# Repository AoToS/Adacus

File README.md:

# Mixed signal PCB with op-amps, filters, ADC/DAC interfaces. ADACUS

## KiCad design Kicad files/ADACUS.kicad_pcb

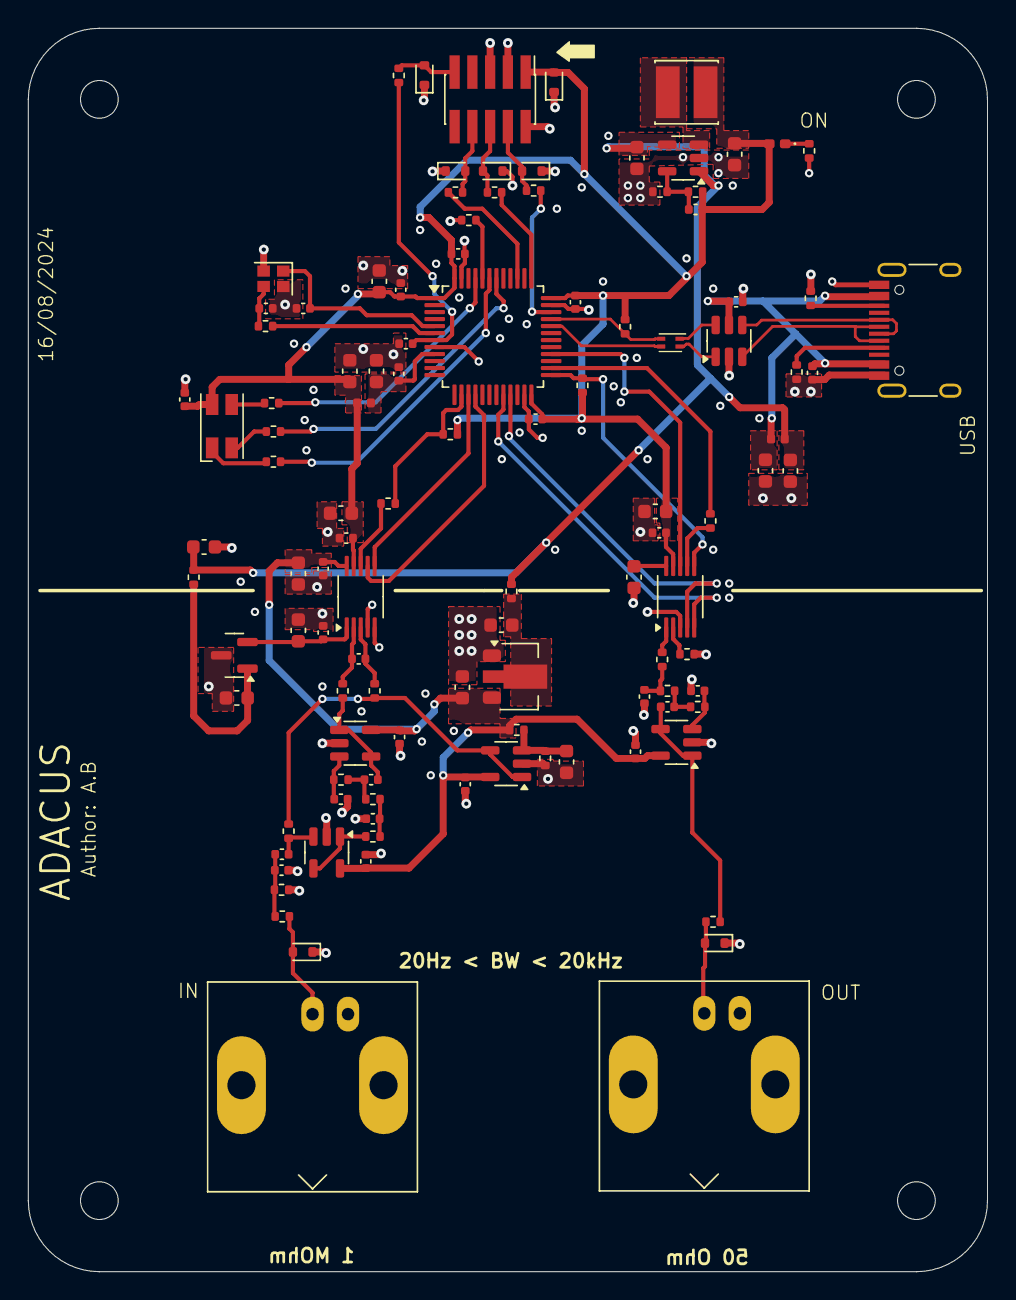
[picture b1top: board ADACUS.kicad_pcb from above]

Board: 4 copper layers, 68.6 x 88.9 mm, 115 parts (0 on the bottom side), 68 nets.

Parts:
C100, C101, C206, C207, C402: 1u; C_0603_1608Metric
C102, C103, C104, C105, C107: 22u; C_0603_1608Metric
C106: DNP; C_0402_1005Metric
C108, C201, C202, C203, C204, C210, C211, C212, C213, C303, C305, C306, C309, C310, C314, C401, C406: 100n; C_0402_1005Metric
C200, C300, C301, C302, C304, C307, C400: 10u; C_0603_1608Metric
C205: 10n; C_0402_1005Metric
C208, C209: 10p; C_0402_1005Metric
C308, C311, C312, C315, C403, C404: 150p; C_0402_1005Metric
C313, C405: 1n; C_0402_1005Metric
D100: LED; D_0402_1005Metric_Pad0.77x0.64mm_HandSolder
D200: ASMB-MTB0-0A3A2; LED_RGB_Wuerth-PLCC4_3.2x2.8mm_150141M173100
D201, D202, D203, D204, D205, D300, D400: PESD3V3L1UB,115; D_SOD-523
FL200: CMF3216F-900-2P-T; L_CommonModeChoke_Coilcraft_0603USB
H100, H101, H102, H103: MountingHole; MountingHole_2.7mm
J200: USB_C_Receptacle_USB2.0_14P; USB_C_Receptacle_HRO_TYPE-C-31-M-12
J201: PinHeader_2x05_P1.27mm_Vertical_SMD
J300, J400: BNC_Amphenol_B6252HB-NPP3G-50_Horizontal
L100, L200: 10n; L_0402_1005Metric
L101: 68u; L_Cenker_CKCS4020
R100: 10R; R_0402_1005Metric
R101: 100k; R_0402_1005Metric
R102: 22k; R_0402_1005Metric
R103, R104, R105: 1K; R_0402_1005Metric
R200, R202, R203: 10K; R_0402_1005Metric
R201, R301, R400: 0R; R_0402_1005Metric
R204: 1k5; R_0402_1005Metric
R205, R206, R207, R208, R300: 49R9; R_0402_1005Metric
R209, R210, R211, R302, R308, R309: 1k; R_0402_1005Metric
R212, R213: 5k1; R_0402_1005Metric
R303, R304: 2M2; R_0402_1005Metric
R305, R306, R307, R402, R403, R404, R405: 6k8; R_0402_1005Metric
R401: 10k; R_0402_1005Metric
U100: HT7533-1; SOT-89-3
U101: TLV62569DBV; SOT-23-5
U102: MCP6001-E/OT; SOT-23-5
U200: STM32F103CBT6; LQFP-48_7x7mm_P0.5mm
U201: USBLC6-2SC6; SOT-23-6
U300, U400: VSSOP-10_3x3mm_P0.5mm
U301: REF3033; SOT-23
U302, U303, U401: MCP6001UT-E/OT; SOT-23-5
Y200: 16MHz; Crystal_SMD_2016-4Pin_2.0x1.6mm

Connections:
+3.3VA: C103.1, C108.2, C304.1, C305.1, C310.2, C314.2, C406.2, R104.1, U100.3 (VOUT), U102.5 (V+), U300.10 (VA), U302.5 (V+), U303.5 (V+), U401.5 (V+)
+3V3: C105.1, C106.1, C200.1, C201.1, C202.1, C203.1, C204.1, C207.1, C211.1, C306.1, C307.1, C400.1, C401.1, D100.2 (A), D200.1 (A), D201.2 (A2), J201.1, L101.2, L200.2, R101.1, R202.1, R203.1, R204.1, U200.1 (VBAT), U200.24 (VDD), U200.36 (VDD), U200.48 (VDD), U300.9 (VIO), U400.9 (AVDD)
+5V: C101.1, C104.1, C300.1, L100.2, R100.1, R300.1, U101.1 (EN), U101.4 (VIN)
/ADC/ADC_IN+: C315.1, R308.2, U300.2 (+IN)
/ADC/ADC_IN-: C315.2, R309.2, U300.3 (-IN)
/ADC/ADC_VREF: C302.1, C303.1, U300.1 (VREF), U301.2 (OUT)
/ADC/IN: D300.2 (A2), J300.1, R302.1
/ADC/IN_AA_BUF_IN: C312.1, R307.2, U303.3 (+)
/ADC/IN_AA_BUF_OUT: C313.2, R308.1, U303.1, U303.4 (-)
/ADC/IN_BUF: C309.2, R304.1, U302.3 (+)
/ADC/IN_BUF_OUT: R305.1, U302.1, U302.4 (-)
/ADC/RF_IN: C308.1, C309.1, R302.2, R303.2
/DAC/DAC_OUT_A: R402.1, U400.1 (VOUT_A)
/DAC/DAC_OUT_B: R401.1, U400.2 (VOUT_B)
/DAC/OUT: D400.2 (A2), J400.1, R405.2
/DAC/OUT_AA_BUF_IN: C404.1, R404.2, U401.3 (+)
/DAC/OUT_AA_BUF_OUT: C405.2, R405.1, U401.1, U401.4 (-)
/DAC/VREF_DC: C402.1, U400.10 (VREF_IN/VREF_OUT)
/MCU/BLUE: D200.2 (BK), R211.2
/MCU/GREEN: D200.3 (GK), R210.2
/MCU/HSE_IN: C208.1, U200.5 (PD0), Y200.1
/MCU/HSE_OUT: R201.2, U200.6 (PD1)
/MCU/MCU_BOOT0: R200.2, U200.44 (BOOT0)
/MCU/MCU_NRST: C210.1, R208.2, U200.7 (NRST)
/MCU/MCU_SWCLK: R206.2, U200.37 (PA14)
/MCU/MCU_SWDIO: R205.2, U200.34 (PA13)
/MCU/MCU_SWO: R207.2, U200.39 (PB3)
/MCU/R205_P10: D202.2 (A2), J201.4, R205.1
/MCU/R206_P9: D203.2 (A2), J201.6, R206.1
/MCU/R207_P8: D204.2 (A2), J201.8, R207.1
/MCU/R208_P16: D205.2 (A2), J201.9, R208.1
/MCU/RED: D200.4 (RK), R209.2
/MCU/TIM4_CH1: R209.1, U200.42 (PB6)
/MCU/TIM4_CH2: R210.1, U200.43 (PB7)
/MCU/TIM4_CH3: R211.1, U200.45 (PB8)
/MCU/USB_CMC_D+: FL200.1, U201.6 (I/O1)
/MCU/USB_CMC_D-: FL200.4, U201.1 (I/O1)
/MCU/USB_CONN_CC1: J200.A5 (CC1), R212.1
/MCU/USB_CONN_CC2: J200.B5 (CC2), R213.1
/MCU/USB_CONN_D+: J200.A6 (D+), J200.B6 (D+), U201.4 (I/O2)
/MCU/USB_CONN_D-: J200.A7 (D-), J200.B7 (D-), U201.3 (I/O2)
/MCU/USB_D+: FL200.2, R204.2, U200.33 (PA12)
/MCU/USB_D-: FL200.3, U200.32 (PA11)
/MCU/XTAL_IN: C209.1, R201.1, Y200.3
/POWER/+5V_FILT: C102.1, R100.2, U100.2 (VIN)
/POWER/FB_BUCK: C106.2, R101.2, R102.1, U101.5 (FB)
/POWER/LED_PWR_+3V3: D100.1 (K), R103.1
/POWER/SW_BUCK: L101.1, U101.3 (SW)
/POWER/VREF_+3V3A: C107.1, R104.2, R105.1, U102.3 (+)
DAC_NCLR: U200.20 (PB2), U400.5 (~CLR)
DAC_NLDAC: U200.21 (PB10), U400.4 (~LDAC)
GND: C100.2, C101.2, C102.2, C103.2, C104.2, C105.2, C107.2, C108.1, C200.2, C201.2, C202.2, C203.2, C204.2, C205.2, C206.2, C207.2, C208.2, C209.2, C210.2, C211.2, C212.2, C213.1, C300.2, C301.2, C302.2, C303.2, C304.2, C305.2, C306.2, C307.2, C308.2, C310.1, C311.2, C312.2, C314.1, C400.2, C401.2, C402.2, C403.2, C404.2, C406.1, D201.1 (A1), D202.1 (A1), D203.1 (A1), D204.1 (A1), D205.1 (A1), D300.1 (A1), D400.1 (A1), J200.B1 (GND), J200.B12 (GND), J200.S1 (SHIELD), J201.2, J201.3, J201.5, J300.2, J400.2, R102.2, R103.2, R105.2, R200.1, R212.2, R213.2, R303.1, R401.2, U100.1 (GND), U101.2 (GND), U102.2 (V-), U200.8 (VSSA), U200.23 (VSS), U200.35 (VSS), U200.47 (VSS), U201.2 (GND), U300.4 (GND), U300.5 (GND), U301.3 (GND), U302.2 (V-), U303.2 (V-), U400.3 (GND), U401.2 (V-), Y200.2, Y200.4
unnamed: C311.1, R305.2, R306.1
unnamed: C313.1, R306.2, R307.1
unnamed: C403.1, R402.2, R403.1
unnamed: C405.1, R403.2, R404.1
unnamed: R301.1, U300.8 (SCLK)
unnamed: C301.1, R300.2, U301.1 (IN)
unnamed: R400.2, U400.7 (SCLK)
SPI1_MISO: U200.16 (PA6), U300.7 (DOUT)
SPI1_NSS: U200.15 (PA5), U300.6 (~CS)
SPI1_SCK: R203.2, R301.2, U200.14 (PA4)
SPI2_MOSI: U200.28 (PB15), U400.8 (DIN)
SPI2_NSS: R202.2, U200.25 (PB12), U400.6 (~SYNC)
SPI2_SCK: R400.1, U200.26 (PB13)
VBUS: C100.1, C212.1, C213.2, J200.A4 (VBUS), J200.A9 (VBUS), J200.B4 (VBUS), J200.B9 (VBUS), L100.1, U201.5 (VBUS)
VCOM: R304.2, R309.1, U102.1, U102.4 (-)
VDDA: C205.1, C206.1, L200.1, U200.9 (VDDA)

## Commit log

2024-03-12 [MAIN] File upload
    Added project files and specificications. Full Schematics for the project. PCB board file [unfinished]
2024-03-13 [FIX] Resistor fix
    Fixed the schematic issue with resistor pinout.
2024-03-13 [FIX] Fixed schematic issue
    Fixed schematic issues with resistor pinout.
2024-03-13 [MAIN] Simulation & Text
    Added simulation for Op-Amp bias generator used. Added small intro for the project documentation.
2024-07-08 [SCH&PCB] Updated schematic and PCB
    Updated netlabels in schematic 2 and 3. Finished the final layout of the PCB routing next.
2024-07-12 [SCH&PCB] FInal PCB update
    Finished PCB layout and routing. Updated silkscreen on top overlay. Added annotations and pin designators on silkscreen.
2024-07-12 Update README.md
    Added final PCB layers and 3D view
2024-07-12 [DOC] Updated read.me
    Added small description for the read.me part of the project
2024-07-12 [DOC]
    Read.me update
2024-07-12 [DOC] Updated read.me
    Updated project description added images and general introduction. Formatted the pinout of MCU and SWD connector.
2024-07-12 Delete README.md
    Deleted the unneccesary file
2024-07-15 [DOC] Further reame update
    Added sections for schematics routing and vias. Added the used track sizes and graphical representations for board stack-up and impedance matching tracks
2024-08-06 [SCH] Added Kicad V8 Schematics
    Added Kicad version 8 schematics for the project. Including a PDF file for all the schematics
2024-08-14 [BCK] Back-up files
    Uploaded back-up files for the setup switch
2024-08-19 [Doc] File Import
2024-08-19 [FILE] Finished board
    Added PCB documents and finished schematics. Project is now done with both Altium and Kicad files uploaded
